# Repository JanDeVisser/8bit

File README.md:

# A Simple Ben Eater Inspired 8-bit computer

Please describe me.

### Register IDs

ID       | Register       |  R W  | Remarks
---------|----------------|-------|--------------
0000 00  | A              |  x x  |
0001 01  | B              |  x x  |
0010 02  | C              |  x x  |
0011 03  | D              |  x x  |
0100 04  | ALU LHS/Result |  x x  | Put: LHS, Get: Result
0101 05  | ALU Operation  |  - x  | Put: RHS, OP0-3: Operation
0110 06  | Instruction    |  - x  |
0111 07  | Mem            |  x x  |
1000 08  | Prog Counter   |  x x  |
1001 09  | SP             |  x x  |
1010 10  | Si             |  x x  |
1011 11  | Di             |  x x  |
1100 12  | TX             |       |
1101 13  |                |       |
1110 14	 | Monitor        |  x -  |
1111 15  | Mem Addr       |  - x  |

### Control Lines

Pin   | Name                   | Description
------|------------------------|-----------------------
1     | `GND`                  | Common Ground
2     | `VCC`                  | +5V Power
3     | `CLK`                  | Square Wave Clock
4     | ~~`CLK`~~              | Reverse Clock
5     | `^CLK`                 | "Burst" Clock at rising edge of CLK
6     | `HLT`                  | Halts clock
7     | ~~`SUS`~~              | Requests Control Unit to cease dispatching instructions.
8     | ~~`XDATA`~~            | 8 bit Data transfer instruction
9     | ~~`XADDR`~~            | 16 bit address transfer instruction
10    | ~~`SACK`~~             | Set by Control Unit as acknowlegement of SUS.
11-14 | `OP0`-`OP3`            | Custom Operation codes used by various instructions. See below.
15    | `RST`                  | Reset
16    | ~~`IO`~~               | In/Out instruction
17-20 | `PUT0`-`PUT3`          | Register ID of the target of a transfer instruction.
21-24 | `GET0`-`GET3`          | Register ID of the source of a transfer instruction.
25-32 | `D0`-`D7`              | Databus
33-40 | `A0`-`A7` / `A8`-`A15` | Address bus

### Operation Codes

#### XADDR

OP0-3 |Function
---|---
`XX01`|Increment source (Get) register
`XX10`|Decrement source (Get) register

#### XDATA

_When moving data between 8- and 16-bit registers:_

OP0-3 |Function
------|--------
`XXX0`|Transfer to/from the LSB of the 16-bit register
`XXX1`|Transfer to/from the MSB of the 16-bit register

_When the target register is ALU Operation (`0x5`):_

OP0-3|Operation
-----|-----------
`0x0`|`ADD`
`0x1`|`ADC`
`0x2`|`SUB`
`0x3`|`SBB`
...|...
`0x8`|`AND`
`0x9`|`OR`
`0xA`|`XOR`
`0xB`|`NOT LHS`
`0xC`|`SHL`
`0xD`|`SHR`
`0xE`|`CLR`
...|...

## N O T E S

### SBB (Subtract with Borrow)

See here: https://en.wikipedia.org/wiki/Carry_flag#Vs._borrow_flag

We use the convention that when subtracting the processor Carry flag is a borrow flag. This is in line with the Z80 and x68.

### 74xxx253 Function Table

As determined by Julian Ilett in https://www.youtube.com/watch?v=15M63Zqkthk

C3-C0 :arrow_down: BA :arrow_right: | 11 | 10 | 01 | 00 | Operation
------|----|----|----|----|-----------
  0x0  | 0  | 0  | 0  | 0  | All Zero
  0x1  | 0  | 0  | 0  | 1  | A NOR B
  0x2  | 0  | 0  | 1  | 0  | A AND (NOT B)
  0x3  | 0  | 0  | 1  | 1  | NOT B
  0x4  | 0  | 1  | 0  | 0  | (NOT A) AND B
  0x5  | 0  | 1  | 0  | 1  | NOT A
  0x6  | 0  | 1  | 1  | 0  | A XOR B
  0x7  | 0  | 1  | 1  | 1  | A NAND B
  0x8  | 1  | 0  | 0  | 0  | A AND B
  0x9  | 1  | 0  | 0  | 1  | A XNOR B
  0xA  | 1  | 0  | 1  | 0  | A
  0xB  | 1  | 0  | 1  | 1  | A OR (NOT B)
  0xC  | 1  | 1  | 0  | 0  | B
  0xD  | 1  | 1  | 0  | 1  | (NOT A) OR B
  0xE  | 1  | 1  | 1  | 0  | A OR B
  0xF  | 1  | 1  | 1  | 1  | All One

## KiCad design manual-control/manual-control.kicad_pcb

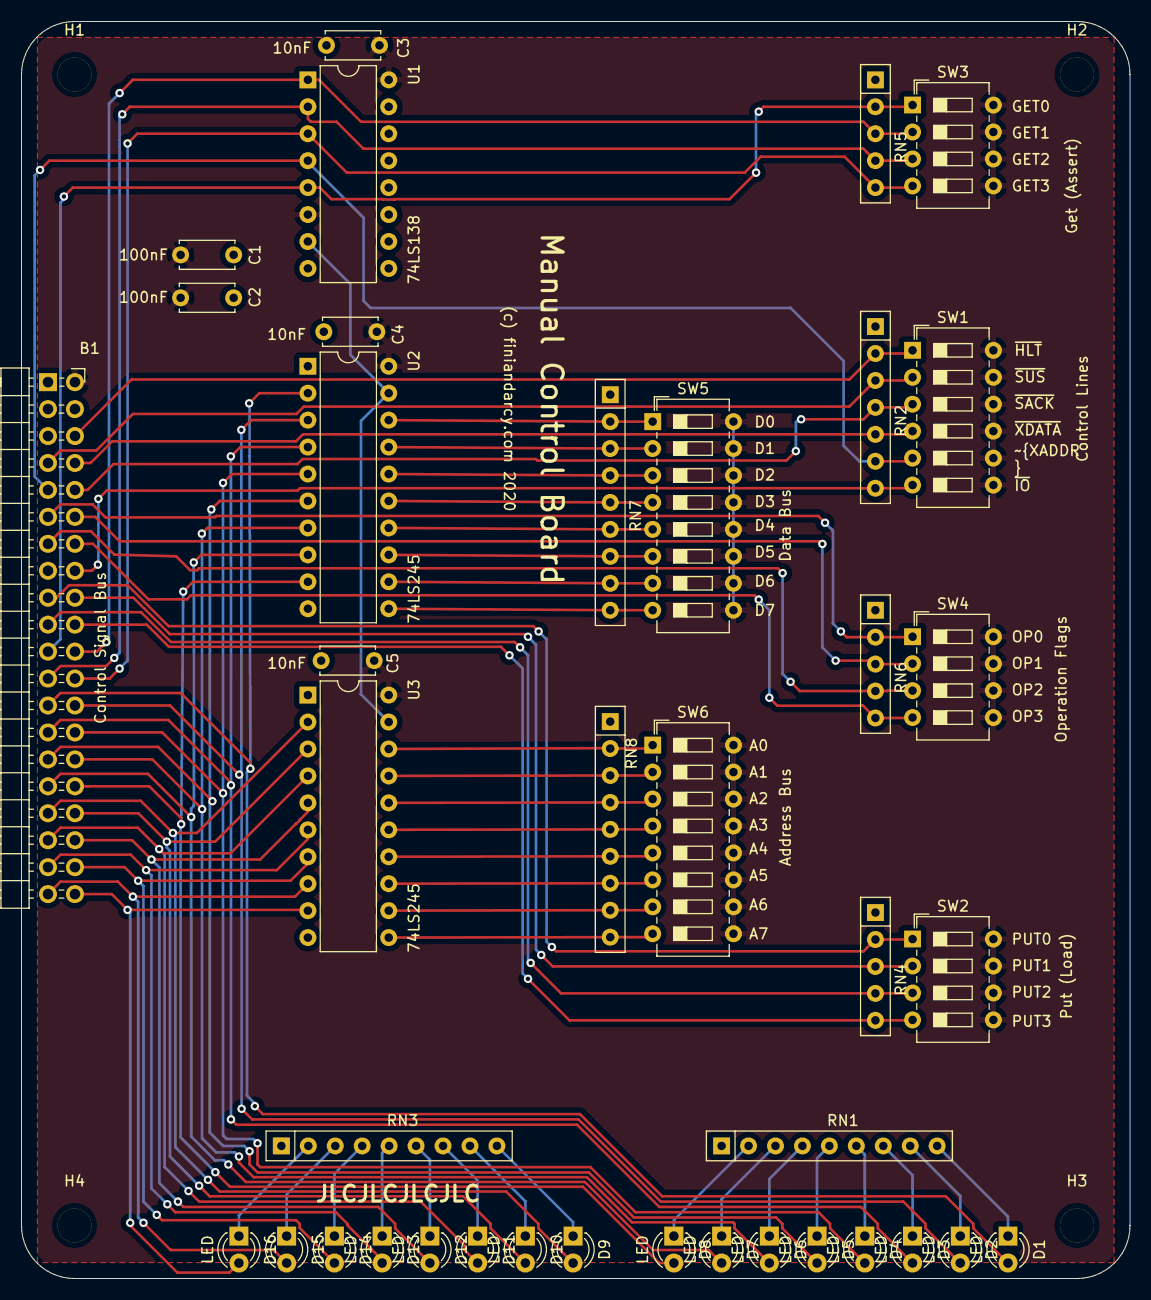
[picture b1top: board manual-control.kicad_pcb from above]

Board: 2 copper layers, 104.5 x 118.5 mm, 43 parts (0 on the bottom side), 69 nets.

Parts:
B1: Control Signal Bus; PinHeader_2x20_P2.54mm_Horizontal_Flipped
C1, C2: 100nF; C_Disc_D5.0mm_W2.5mm_P5.00mm
C3, C4, C5: 10nF; C_Disc_D5.0mm_W2.5mm_P5.00mm
D1, D2, D3, D4, D5, D6, D7, D8, D9, D10, D11, D12, D13, D14, D15, D16: LED; LED_D3.0mm
H1, H2, H3, H4: H; MountingHole_3.2mm_M3
RN1, RN3, RN7, RN8: 1K; R_Array_SIP9
RN2: 1K; R_Array_SIP7
RN4, RN5, RN6: 1K; R_Array_SIP5
SW1: Control Lines; SW_DIP_SPSTx06_Slide_6.7x16.8mm_W7.62mm_P2.54mm_LowProfile
SW2: Put (Load); SW_DIP_SPSTx04_Slide_6.7x11.72mm_W7.62mm_P2.54mm_LowProfile
SW3: Get (Assert); SW_DIP_SPSTx04_Slide_6.7x11.72mm_W7.62mm_P2.54mm_LowProfile
SW4: Operation Flags; SW_DIP_SPSTx04_Slide_6.7x11.72mm_W7.62mm_P2.54mm_LowProfile
SW5: Data Bus; SW_DIP_SPSTx08_Slide_6.7x21.88mm_W7.62mm_P2.54mm_LowProfile
SW6: Address Bus; SW_DIP_SPSTx08_Slide_6.7x21.88mm_W7.62mm_P2.54mm_LowProfile
U1: 74LS138; DIP-16_W7.62mm
U2, U3: 74LS245; DIP-20_W7.62mm

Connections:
/A0: B1.33, D9.2, U3.2
/A1: B1.34, D10.2, U3.3
/A2: B1.35, D11.2, U3.4
/A3: B1.36, D12.2, U3.5
/A4: B1.37, D13.2, U3.6
/A5: B1.38, D14.2, U3.7
/A6: B1.39, D15.2, U3.8
/A7: B1.40, D16.2, U3.9
/D0: B1.25, D1.2, U2.2
/D1: B1.26, D2.2, U2.3
/D2: B1.27, D3.2, U2.4
/D3: B1.28, D4.2, U2.5
/D4: B1.29, D5.2, U2.6
/D5: B1.30, D6.2, U2.7
/D6: B1.31, D7.2, U2.8
/D7: B1.32, D8.2, U2.9
/GET0: B1.21, RN5.2, SW3.1, U1.5
/GET1: B1.22, RN5.3, SW3.2, U1.1
/GET2: B1.23, RN5.4, SW3.3, U1.2
/GET3: B1.24, RN5.5, SW3.4, U1.3
/OP0: B1.11, RN6.2, SW4.1
/OP1: B1.12, RN6.3, SW4.2
/OP2: B1.13, RN6.4, SW4.3
/OP3: B1.14, RN6.5, SW4.4
/PUT0: B1.17, RN4.2, SW2.1
/PUT1: B1.18, RN4.3, SW2.2
/PUT2: B1.19, RN4.4, SW2.3
/PUT3: B1.20, RN4.5, SW2.4
/~Get: U1.7, U2.19, U3.19
/~HLT: B1.6, RN2.2, SW1.1
/~IO: B1.16, RN2.7, SW1.6
/~SACK: B1.10, RN2.4, SW1.3
/~SUS: B1.7, RN2.3, SW1.2
/~XADDR: B1.9, RN2.6, SW1.5, U1.4
/~XDATA: B1.8, RN2.5, SW1.4
GND: B1.1, C1.2, C2.2, C3.1, C4.1, C5.1, H1.1, H2.1, H3.1, H4.1, RN1.1, RN2.1, RN3.1, RN4.1, RN5.1, RN6.1, RN7.1, RN8.1, U1.8, U2.1, U2.10, U3.1, U3.10
unnamed: D1.1, RN1.9
unnamed: D2.1, RN1.8
unnamed: D3.1, RN1.7
unnamed: D4.1, RN1.6
unnamed: D5.1, RN1.5
unnamed: D6.1, RN1.4
unnamed: D7.1, RN1.3
unnamed: D8.1, RN1.2
unnamed: D9.1, RN3.9
unnamed: D10.1, RN3.8
unnamed: D11.1, RN3.7
unnamed: D12.1, RN3.6
unnamed: D13.1, RN3.5
unnamed: D14.1, RN3.4
unnamed: D15.1, RN3.3
unnamed: D16.1, RN3.2
unnamed: RN7.2, SW5.1, U2.18
unnamed: RN7.3, SW5.2, U2.17
unnamed: RN7.4, SW5.3, U2.16
unnamed: RN7.5, SW5.4, U2.15
unnamed: RN7.6, SW5.5, U2.14
unnamed: RN7.7, SW5.6, U2.13
unnamed: RN7.8, SW5.7, U2.12
unnamed: RN7.9, SW5.8, U2.11
unnamed: RN8.2, SW6.1, U3.18
unnamed: RN8.3, SW6.2, U3.17
unnamed: RN8.4, SW6.3, U3.16
unnamed: RN8.5, SW6.4, U3.15
unnamed: RN8.6, SW6.5, U3.14
unnamed: RN8.7, SW6.6, U3.13
unnamed: RN8.8, SW6.7, U3.12
unnamed: RN8.9, SW6.8, U3.11
VCC: B1.2, C1.1, C2.1, C3.2, C4.2, C5.2, SW1.7, SW1.8, SW1.9, SW1.10, SW1.11, SW1.12, SW2.5, SW2.6, SW2.7, SW2.8, SW3.5, SW3.6, SW3.7, SW3.8, SW4.5, SW4.6, SW4.7, SW4.8, SW5.9, SW5.10, SW5.11, SW5.12, SW5.13, SW5.14, SW5.15, SW5.16, SW6.9, SW6.10, SW6.11, SW6.12, SW6.13, SW6.14, SW6.15, SW6.16, U1.6, U1.16, U2.20, U3.20

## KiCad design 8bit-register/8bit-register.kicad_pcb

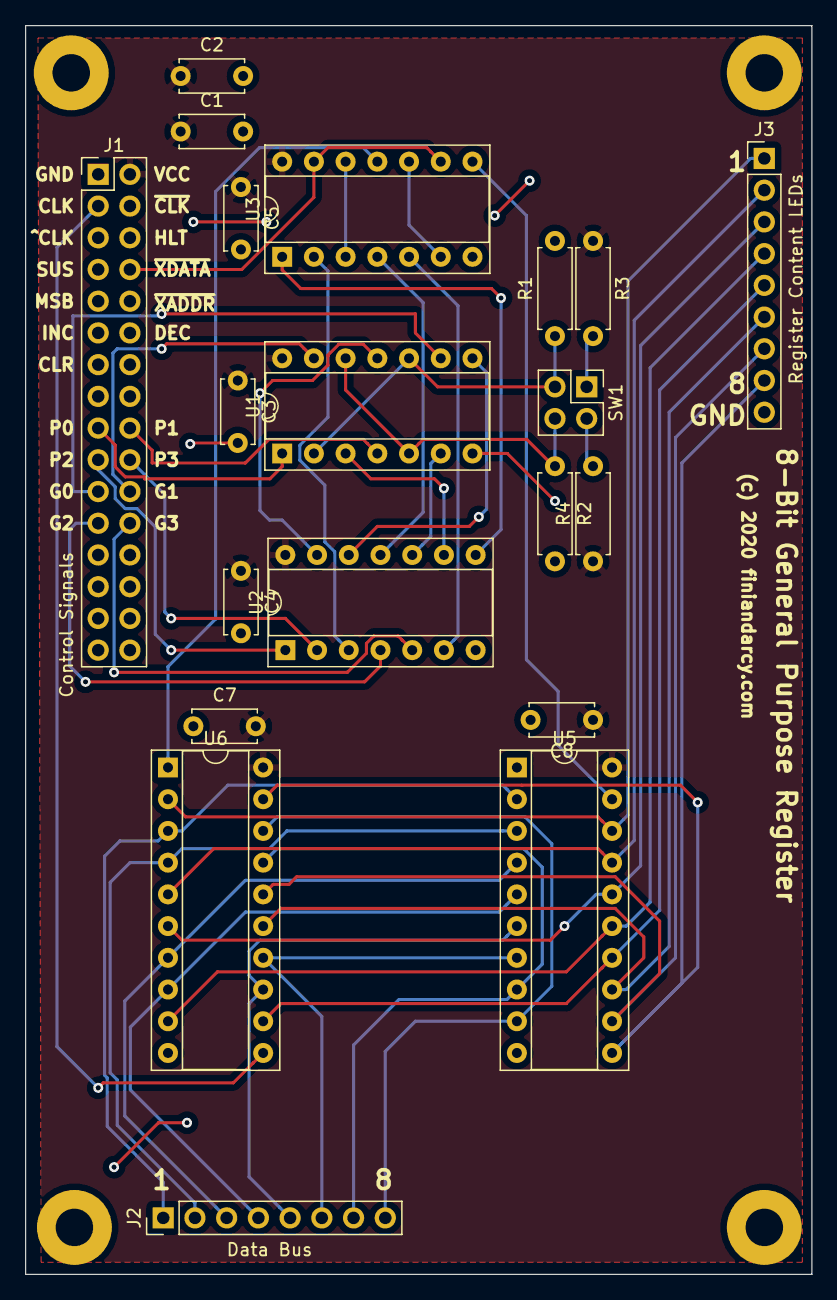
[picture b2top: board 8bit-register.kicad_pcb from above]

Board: 2 copper layers, 63.0 x 100.0 mm, 24 parts (0 on the bottom side), 44 nets.

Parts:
C1, C2: 0.1uF; C_Disc_D5.0mm_W2.5mm_P5.00mm
C3, C4, C5, C7, C8: 10nF; C_Disc_D5.0mm_W2.5mm_P5.00mm
J1: Control Signals; PinHeader_2x16_P2.54mm_Vertical
J2: Data Bus; PinHeader_1x08_P2.54mm_Vertical
J3: Register Content LEDs; PinHeader_1x09_P2.54mm_Vertical
M1, M2, M3, M4: MountingHole_3mm_Pad
R1, R2, R3: 3K3; R_Axial_DIN0207_L6.3mm_D2.5mm_P7.62mm_Horizontal
R4: 3k3; R_Axial_DIN0207_L6.3mm_D2.5mm_P7.62mm_Horizontal
SW1: RegisterID; PinHeader_2x02_P2.54mm_Vertical
U1: 74LS86; DIP-14_W7.62mm_Socket
U2, U3: 74LS32; DIP-14_W7.62mm_Socket
U5: 74LS245; DIP-20_W7.62mm_Socket
U6: 74LS377; DIP-20_W7.62mm_Socket

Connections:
/B0: J2.1, U5.2, U6.3
/B1: J2.2, U5.3, U6.4
/B2: J2.3, U5.4, U6.7
/B3: J2.4, U5.5, U6.8
/B4: J2.5, U5.6, U6.13
/B5: J2.6, U5.7, U6.14
/B6: J2.7, U5.8, U6.17
/B7: J2.8, U5.9, U6.18
/CLK: J1.3, U6.11
/Conf0: R1.1, SW1.3, U1.2, U1.10
/Conf1: R2.1, SW1.4, U1.5, U1.12
/GET0: J1.21, U1.9
/GET1: J1.22, U1.13
/GET2: J1.23, U2.4
/GET3: J1.24, U2.5
/PUT0: J1.17, U1.1
/PUT1: J1.18, U1.4
/PUT2: J1.19, U2.1
/PUT3: J1.20, U2.2
/T0: J3.1, U5.18, U6.2
/T1: J3.2, U5.17, U6.5
/T2: J3.3, U5.16, U6.6
/T3: J3.4, U5.15, U6.9
/T4: J3.5, U5.14, U6.12
/T5: J3.6, U5.13, U6.15
/T6: J3.7, U5.12, U6.16
/T7: J3.8, U5.11, U6.19
/~Get: U3.8, U5.19
/~Put: U3.11, U6.1
/~XDATA: J1.8, U3.9, U3.13
GND: C1.2, C2.2, C3.2, C4.2, C5.2, C7.1, C8.2, J1.1, J3.9, R1.2, R2.2, U1.7, U2.7, U3.7, U5.1, U5.10, U6.10
unnamed: R3.2, SW1.1
unnamed: R4.2, SW1.2
unnamed: U1.3, U2.9
unnamed: U1.6, U2.10
unnamed: U1.8, U2.12
unnamed: U1.11, U2.13
unnamed: U2.3, U3.2
unnamed: U2.6, U3.5
unnamed: U2.8, U3.1
unnamed: U2.11, U3.4
unnamed: U3.6, U3.10
unnamed: U3.3, U3.12
VCC: C1.1, C2.1, C3.1, C4.1, C5.1, C7.2, C8.1, J1.2, R3.1, R4.1, U1.14, U2.14, U3.14, U5.20, U6.20

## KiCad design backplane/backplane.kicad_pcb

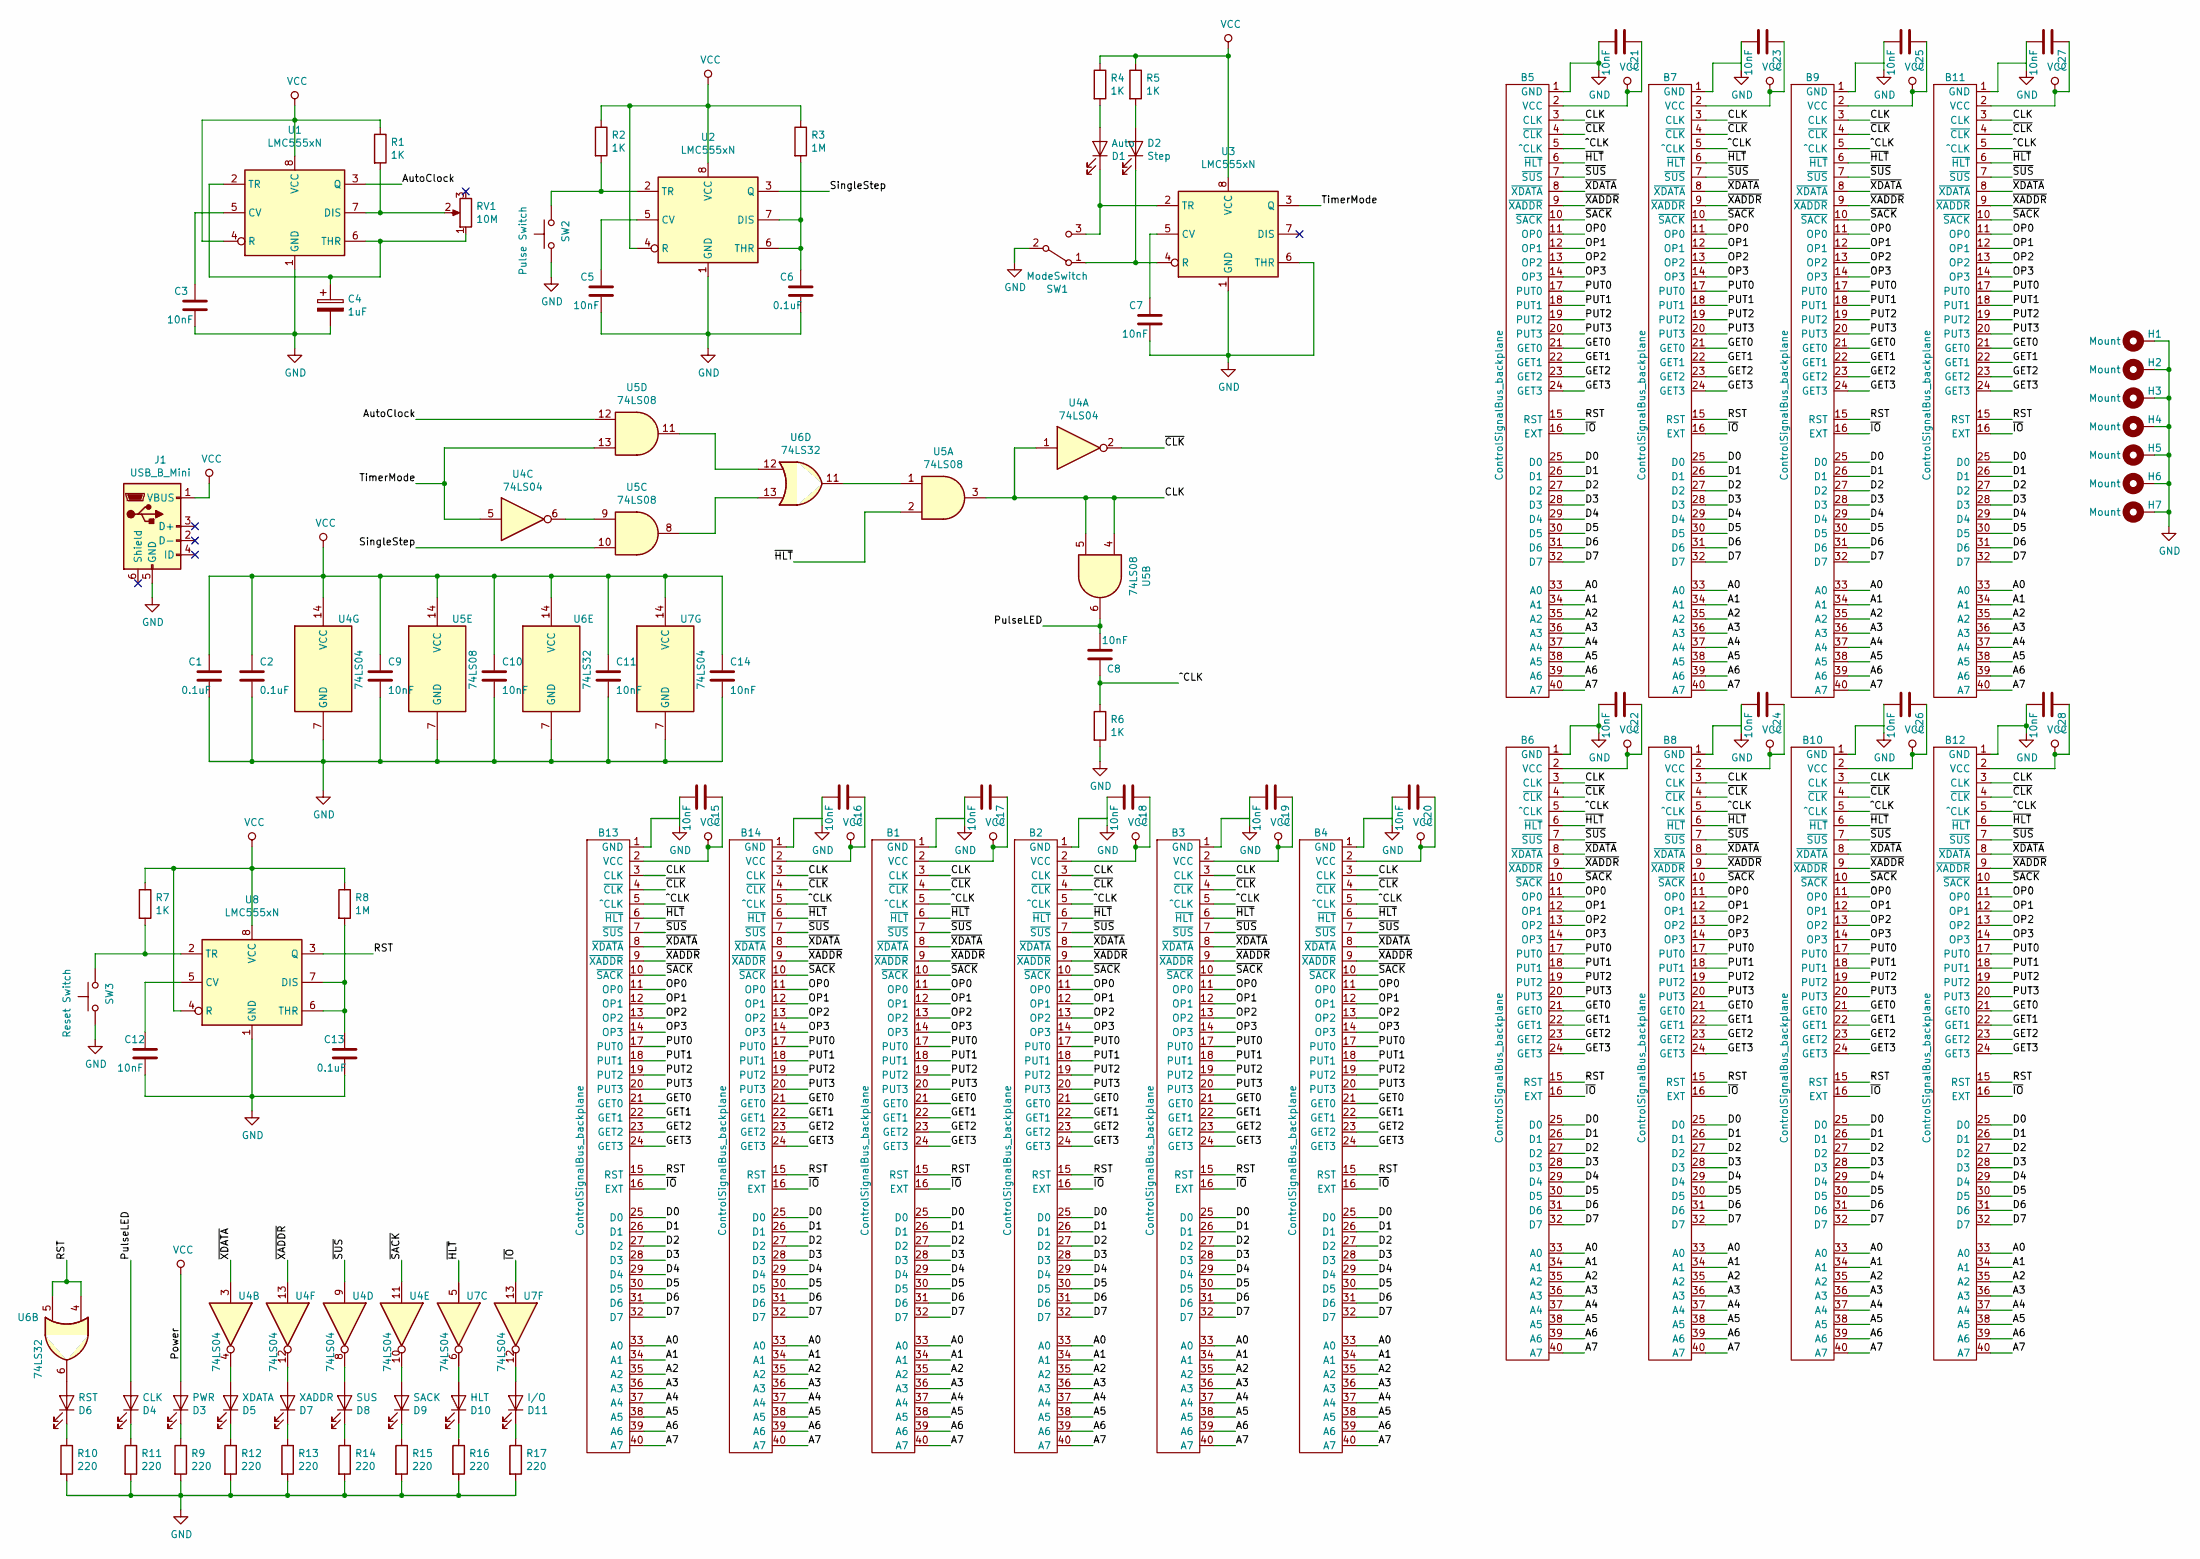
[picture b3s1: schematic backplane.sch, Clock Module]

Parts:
B1, B2, B3, B4, B5, B6, B7, B8, B9, B10, B11, B12, B13, B14: ControlSignalBus_backplane; PinSocket_2x20_P2.54mm_Vertical
C1, C2, C6, C13: 0.1uF; C_Disc_D5.0mm_W2.5mm_P5.00mm
C3, C5, C7, C8, C9, C10, C11, C12, C14, C15, C16, C17, C18, C19, C20, C21, C22, C23, C24, C25, C26, C27, C28: 10nF; C_Disc_D5.0mm_W2.5mm_P5.00mm
C4: 1uF; C_Radial_D5.0mm_H11.0mm_P2.00mm
D1: Auto; LED_D5.0mm
D2: Step; LED_D5.0mm
D3: PWR; LED_D5.0mm
D4: CLK; LED_D5.0mm
D5: XDATA; LED_D5.0mm
D6: RST; LED_D5.0mm
D7: XADDR; LED_D5.0mm
D8: SUS; LED_D5.0mm
D9: SACK; LED_D5.0mm
D10: HLT; LED_D5.0mm
D11: I/O; LED_D5.0mm
H1, H2, H3, H4, H5, H6, H7: Mount; MountingHole_3.2mm_M3_Pad
J1: USB_B_Mini; TE_2172034-1
R1, R2, R4, R5, R6, R7: 1K; R_Axial_DIN0207_L6.3mm_D2.5mm_P7.62mm_Horizontal
R3, R8: 1M; R_Axial_DIN0207_L6.3mm_D2.5mm_P7.62mm_Horizontal
R9, R10, R11, R12, R13, R14, R15, R16, R17: 220; R_Axial_DIN0207_L6.3mm_D2.5mm_P7.62mm_Horizontal
RV1: 10M; TT-P160KN-0QC15A
SW1: ModeSwitch; 400MSP1R6BLKM6RE
SW2: Pulse Switch; KS11R22CQD
SW3: Reset Switch; KS11R22CQD
U1, U2, U3, U8: LMC555xN; DIP-8_W7.62mm_Socket
U4, U7: 74LS04; DIP-14_W7.62mm_Socket
U5: 74LS08; DIP-14_W7.62mm_Socket
U6: 74LS32; DIP-14_W7.62mm_Socket

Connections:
/A0: B1.33 (A0), B2.33 (A0), B3.33 (A0), B4.33 (A0), B5.33 (A0), B6.33 (A0), B7.33 (A0), B8.33 (A0), B9.33 (A0), B10.33 (A0), B11.33 (A0), B12.33 (A0), B13.33 (A0), B14.33 (A0)
/A1: B1.34 (A1), B2.34 (A1), B3.34 (A1), B4.34 (A1), B5.34 (A1), B6.34 (A1), B7.34 (A1), B8.34 (A1), B9.34 (A1), B10.34 (A1), B11.34 (A1), B12.34 (A1), B13.34 (A1), B14.34 (A1)
/A2: B1.35 (A2), B2.35 (A2), B3.35 (A2), B4.35 (A2), B5.35 (A2), B6.35 (A2), B7.35 (A2), B8.35 (A2), B9.35 (A2), B10.35 (A2), B11.35 (A2), B12.35 (A2), B13.35 (A2), B14.35 (A2)
/A3: B1.36 (A3), B2.36 (A3), B3.36 (A3), B4.36 (A3), B5.36 (A3), B6.36 (A3), B7.36 (A3), B8.36 (A3), B9.36 (A3), B10.36 (A3), B11.36 (A3), B12.36 (A3), B13.36 (A3), B14.36 (A3)
/A4: B1.37 (A4), B2.37 (A4), B3.37 (A4), B4.37 (A4), B5.37 (A4), B6.37 (A4), B7.37 (A4), B8.37 (A4), B9.37 (A4), B10.37 (A4), B11.37 (A4), B12.37 (A4), B13.37 (A4), B14.37 (A4)
/A5: B1.38 (A5), B2.38 (A5), B3.38 (A5), B4.38 (A5), B5.38 (A5), B6.38 (A5), B7.38 (A5), B8.38 (A5), B9.38 (A5), B10.38 (A5), B11.38 (A5), B12.38 (A5), B13.38 (A5), B14.38 (A5)
/A6: B1.39 (A6), B2.39 (A6), B3.39 (A6), B4.39 (A6), B5.39 (A6), B6.39 (A6), B7.39 (A6), B8.39 (A6), B9.39 (A6), B10.39 (A6), B11.39 (A6), B12.39 (A6), B13.39 (A6), B14.39 (A6)
/A7: B1.40 (A7), B2.40 (A7), B3.40 (A7), B4.40 (A7), B5.40 (A7), B6.40 (A7), B7.40 (A7), B8.40 (A7), B9.40 (A7), B10.40 (A7), B11.40 (A7), B12.40 (A7), B13.40 (A7), B14.40 (A7)
/AutoClock: U1.3 (Q), U5.12
/CLK: B1.3 (CLK), B2.3 (CLK), B3.3 (CLK), B4.3 (CLK), B5.3 (CLK), B6.3 (CLK), B7.3 (CLK), B8.3 (CLK), B9.3 (CLK), B10.3 (CLK), B11.3 (CLK), B12.3 (CLK), B13.3 (CLK), B14.3 (CLK), U4.1, U5.3, U5.4, U5.5
/D0: B1.25 (D0), B2.25 (D0), B3.25 (D0), B4.25 (D0), B5.25 (D0), B6.25 (D0), B7.25 (D0), B8.25 (D0), B9.25 (D0), B10.25 (D0), B11.25 (D0), B12.25 (D0), B13.25 (D0), B14.25 (D0)
/D1: B1.26 (D1), B2.26 (D1), B3.26 (D1), B4.26 (D1), B5.26 (D1), B6.26 (D1), B7.26 (D1), B8.26 (D1), B9.26 (D1), B10.26 (D1), B11.26 (D1), B12.26 (D1), B13.26 (D1), B14.26 (D1)
/D2: B1.27 (D2), B2.27 (D2), B3.27 (D2), B4.27 (D2), B5.27 (D2), B6.27 (D2), B7.27 (D2), B8.27 (D2), B9.27 (D2), B10.27 (D2), B11.27 (D2), B12.27 (D2), B13.27 (D2), B14.27 (D2)
/D3: B1.28 (D3), B2.28 (D3), B3.28 (D3), B4.28 (D3), B5.28 (D3), B6.28 (D3), B7.28 (D3), B8.28 (D3), B9.28 (D3), B10.28 (D3), B11.28 (D3), B12.28 (D3), B13.28 (D3), B14.28 (D3)
/D4: B1.29 (D4), B2.29 (D4), B3.29 (D4), B4.29 (D4), B5.29 (D4), B6.29 (D4), B7.29 (D4), B8.29 (D4), B9.29 (D4), B10.29 (D4), B11.29 (D4), B12.29 (D4), B13.29 (D4), B14.29 (D4)
/D5: B1.30 (D5), B2.30 (D5), B3.30 (D5), B4.30 (D5), B5.30 (D5), B6.30 (D5), B7.30 (D5), B8.30 (D5), B9.30 (D5), B10.30 (D5), B11.30 (D5), B12.30 (D5), B13.30 (D5), B14.30 (D5)
/D6: B1.31 (D6), B2.31 (D6), B3.31 (D6), B4.31 (D6), B5.31 (D6), B6.31 (D6), B7.31 (D6), B8.31 (D6), B9.31 (D6), B10.31 (D6), B11.31 (D6), B12.31 (D6), B13.31 (D6), B14.31 (D6)
/D7: B1.32 (D7), B2.32 (D7), B3.32 (D7), B4.32 (D7), B5.32 (D7), B6.32 (D7), B7.32 (D7), B8.32 (D7), B9.32 (D7), B10.32 (D7), B11.32 (D7), B12.32 (D7), B13.32 (D7), B14.32 (D7)
/GET0: B1.21 (GET0), B2.21 (GET0), B3.21 (GET0), B4.21 (GET0), B5.21 (GET0), B6.21 (GET0), B7.21 (GET0), B8.21 (GET0), B9.21 (GET0), B10.21 (GET0), B11.21 (GET0), B12.21 (GET0), B13.21 (GET0), B14.21 (GET0)
/GET1: B1.22 (GET1), B2.22 (GET1), B3.22 (GET1), B4.22 (GET1), B5.22 (GET1), B6.22 (GET1), B7.22 (GET1), B8.22 (GET1), B9.22 (GET1), B10.22 (GET1), B11.22 (GET1), B12.22 (GET1), B13.22 (GET1), B14.22 (GET1)
/GET2: B1.23 (GET2), B2.23 (GET2), B3.23 (GET2), B4.23 (GET2), B5.23 (GET2), B6.23 (GET2), B7.23 (GET2), B8.23 (GET2), B9.23 (GET2), B10.23 (GET2), B11.23 (GET2), B12.23 (GET2), B13.23 (GET2), B14.23 (GET2)
/GET3: B1.24 (GET3), B2.24 (GET3), B3.24 (GET3), B4.24 (GET3), B5.24 (GET3), B6.24 (GET3), B7.24 (GET3), B8.24 (GET3), B9.24 (GET3), B10.24 (GET3), B11.24 (GET3), B12.24 (GET3), B13.24 (GET3), B14.24 (GET3)
/OP0: B1.11 (OP0), B2.11 (OP0), B3.11 (OP0), B4.11 (OP0), B5.11 (OP0), B6.11 (OP0), B7.11 (OP0), B8.11 (OP0), B9.11 (OP0), B10.11 (OP0), B11.11 (OP0), B12.11 (OP0), B13.11 (OP0), B14.11 (OP0)
/OP1: B1.12 (OP1), B2.12 (OP1), B3.12 (OP1), B4.12 (OP1), B5.12 (OP1), B6.12 (OP1), B7.12 (OP1), B8.12 (OP1), B9.12 (OP1), B10.12 (OP1), B11.12 (OP1), B12.12 (OP1), B13.12 (OP1), B14.12 (OP1)
/OP2: B1.13 (OP2), B2.13 (OP2), B3.13 (OP2), B4.13 (OP2), B5.13 (OP2), B6.13 (OP2), B7.13 (OP2), B8.13 (OP2), B9.13 (OP2), B10.13 (OP2), B11.13 (OP2), B12.13 (OP2), B13.13 (OP2), B14.13 (OP2)
/OP3: B1.14 (OP3), B2.14 (OP3), B3.14 (OP3), B4.14 (OP3), B5.14 (OP3), B6.14 (OP3), B7.14 (OP3), B8.14 (OP3), B9.14 (OP3), B10.14 (OP3), B11.14 (OP3), B12.14 (OP3), B13.14 (OP3), B14.14 (OP3)
/PUT0: B1.17 (PUT0), B2.17 (PUT0), B3.17 (PUT0), B4.17 (PUT0), B5.17 (PUT0), B6.17 (PUT0), B7.17 (PUT0), B8.17 (PUT0), B9.17 (PUT0), B10.17 (PUT0), B11.17 (PUT0), B12.17 (PUT0), B13.17 (PUT0), B14.17 (PUT0)
/PUT1: B1.18 (PUT1), B2.18 (PUT1), B3.18 (PUT1), B4.18 (PUT1), B5.18 (PUT1), B6.18 (PUT1), B7.18 (PUT1), B8.18 (PUT1), B9.18 (PUT1), B10.18 (PUT1), B11.18 (PUT1), B12.18 (PUT1), B13.18 (PUT1), B14.18 (PUT1)
/PUT2: B1.19 (PUT2), B2.19 (PUT2), B3.19 (PUT2), B4.19 (PUT2), B5.19 (PUT2), B6.19 (PUT2), B7.19 (PUT2), B8.19 (PUT2), B9.19 (PUT2), B10.19 (PUT2), B11.19 (PUT2), B12.19 (PUT2), B13.19 (PUT2), B14.19 (PUT2)
/PUT3: B1.20 (PUT3), B2.20 (PUT3), B3.20 (PUT3), B4.20 (PUT3), B5.20 (PUT3), B6.20 (PUT3), B7.20 (PUT3), B8.20 (PUT3), B9.20 (PUT3), B10.20 (PUT3), B11.20 (PUT3), B12.20 (PUT3), B13.20 (PUT3), B14.20 (PUT3)
/PulseLED: C8.2, D4.2 (A), U5.6
/RST: B1.15 (RST), B2.15 (RST), B3.15 (RST), B4.15 (RST), B5.15 (RST), B6.15 (RST), B7.15 (RST), B8.15 (RST), B9.15 (RST), B10.15 (RST), B11.15 (RST), B12.15 (RST), B13.15 (RST), B14.15 (RST), U6.4, U6.5, U8.3 (Q)
/SingleStep: U2.3 (Q), U5.10
/TimerMode: U3.3 (Q), U4.5, U5.13
/^CLK: B1.5 (^CLK), B2.5 (^CLK), B3.5 (^CLK), B4.5 (^CLK), B5.5 (^CLK), B6.5 (^CLK), B7.5 (^CLK), B8.5 (^CLK), B9.5 (^CLK), B10.5 (^CLK), B11.5 (^CLK), B12.5 (^CLK), B13.5 (^CLK), B14.5 (^CLK), C8.1, R6.1
/~CLK: B1.4 (~CLK), B2.4 (~CLK), B3.4 (~CLK), B4.4 (~CLK), B5.4 (~CLK), B6.4 (~CLK), B7.4 (~CLK), B8.4 (~CLK), B9.4 (~CLK), B10.4 (~CLK), B11.4 (~CLK), B12.4 (~CLK), B13.4 (~CLK), B14.4 (~CLK), U4.2
/~HLT: B1.6 (~HLT), B2.6 (~HLT), B3.6 (~HLT), B4.6 (~HLT), B5.6 (~HLT), B6.6 (~HLT), B7.6 (~HLT), B8.6 (~HLT), B9.6 (~HLT), B10.6 (~HLT), B11.6 (~HLT), B12.6 (~HLT), B13.6 (~HLT), B14.6 (~HLT), U5.2, U7.5
/~IO: B1.16 (EXT), B2.16 (EXT), B3.16 (EXT), B4.16 (EXT), B5.16 (EXT), B6.16 (EXT), B7.16 (EXT), B8.16 (EXT), B9.16 (EXT), B10.16 (EXT), B11.16 (EXT), B12.16 (EXT), B13.16 (EXT), B14.16 (EXT), U7.13
/~SACK: B1.10 (~SACK), B2.10 (~SACK), B3.10 (~SACK), B4.10 (~SACK), B5.10 (~SACK), B6.10 (~SACK), B7.10 (~SACK), B8.10 (~SACK), B9.10 (~SACK), B10.10 (~SACK), B11.10 (~SACK), B12.10 (~SACK), B13.10 (~SACK), B14.10 (~SACK), U4.11
/~SUS: B1.7 (~SUS), B2.7 (~SUS), B3.7 (~SUS), B4.7 (~SUS), B5.7 (~SUS), B6.7 (~SUS), B7.7 (~SUS), B8.7 (~SUS), B9.7 (~SUS), B10.7 (~SUS), B11.7 (~SUS), B12.7 (~SUS), B13.7 (~SUS), B14.7 (~SUS), U4.9
/~XADDR: B1.9 (~XADDR), B2.9 (~XADDR), B3.9 (~XADDR), B4.9 (~XADDR), B5.9 (~XADDR), B6.9 (~XADDR), B7.9 (~XADDR), B8.9 (~XADDR), B9.9 (~XADDR), B10.9 (~XADDR), B11.9 (~XADDR), B12.9 (~XADDR), B13.9 (~XADDR), B14.9 (~XADDR), U4.13
/~XDATA: B1.8 (~XDATA), B2.8 (~XDATA), B3.8 (~XDATA), B4.8 (~XDATA), B5.8 (~XDATA), B6.8 (~XDATA), B7.8 (~XDATA), B8.8 (~XDATA), B9.8 (~XDATA), B10.8 (~XDATA), B11.8 (~XDATA), B12.8 (~XDATA), B13.8 (~XDATA), B14.8 (~XDATA), U4.3
GND: B1.1 (GND), B2.1 (GND), B3.1 (GND), B4.1 (GND), B5.1 (GND), B6.1 (GND), B7.1 (GND), B8.1 (GND), B9.1 (GND), B10.1 (GND), B11.1 (GND), B12.1 (GND), B13.1 (GND), B14.1 (GND), C1.2, C2.2, C3.2, C4.2, C5.2, C6.2, C7.2, C9.2, C10.2, C11.2, C12.2, C13.2, C14.2, C15.2, C16.2, C17.2, C18.2, C19.2, C20.2, C21.2, C22.2, C23.2, C24.2, C25.2, C26.2, C27.2, C28.2, H1.1, H2.1, H3.1, H4.1, H5.1, H6.1, H7.1, J1.5 (GND), R6.2, R9.2, R10.2, R11.2, R12.2, R13.2, R14.2, R15.2, R16.2, R17.2, SW1.2 (B), SW2.1, SW3.1, U1.1 (GND), U2.1 (GND), U3.1 (GND), U3.6 (THR), U4.7 (GND), U5.7 (GND), U6.7 (GND), U7.7 (GND), U8.1 (GND)
unnamed: C3.1, U1.5 (CV)
unnamed: C4.1, RV1.1, U1.2 (TR), U1.6 (THR)
unnamed: C5.1, U2.5 (CV)
unnamed: C6.1, R3.2, U2.6 (THR), U2.7 (DIS)
unnamed: C7.1, U3.5 (CV)
unnamed: C12.1, U8.5 (CV)
unnamed: C13.1, R8.2, U8.6 (THR), U8.7 (DIS)
unnamed: D1.1 (K), SW1.3 (C), U3.2 (TR)
unnamed: D1.2 (A), R4.2
unnamed: D2.1 (K), SW1.1 (A), U3.4 (R)
unnamed: D2.2 (A), R5.2
unnamed: D3.1 (K), R9.1
unnamed: D4.1 (K), R11.1
unnamed: D5.1 (K), R12.1
unnamed: D5.2 (A), U4.4
unnamed: D6.1 (K), R10.1
unnamed: D6.2 (A), U6.6
unnamed: D7.1 (K), R13.1
unnamed: D7.2 (A), U4.12
unnamed: D8.1 (K), R14.1
unnamed: D8.2 (A), U4.8
unnamed: D9.1 (K), R15.1
unnamed: D9.2 (A), U4.10
unnamed: D10.1 (K), R16.1
unnamed: D10.2 (A), U7.6
unnamed: D11.1 (K), R17.1
unnamed: D11.2 (A), U7.12
unnamed: R1.2, RV1.2, U1.7 (DIS)
unnamed: R2.2, SW2.2, U2.2 (TR)
unnamed: R7.2, SW3.2, U8.2 (TR)
unnamed: U4.6, U5.9
unnamed: U5.1, U6.11
unnamed: U5.8, U6.13
unnamed: U5.11, U6.12
VCC: B1.2 (VCC), B2.2 (VCC), B3.2 (VCC), B4.2 (VCC), B5.2 (VCC), B6.2 (VCC), B7.2 (VCC), B8.2 (VCC), B9.2 (VCC), B10.2 (VCC), B11.2 (VCC), B12.2 (VCC), B13.2 (VCC), B14.2 (VCC), C1.1, C2.1, C9.1, C10.1, C11.1, C14.1, C15.1, C16.1, C17.1, C18.1, C19.1, C20.1, C21.1, C22.1, C23.1, C24.1, C25.1, C26.1, C27.1, C28.1, D3.2 (A), J1.1 (VBUS), R1.1, R2.1, R3.1, R4.1, R5.1, R7.1, R8.1, U1.4 (R), U1.8 (VCC), U2.4 (R), U2.8 (VCC), U3.8 (VCC), U4.14 (VCC), U5.14 (VCC), U6.14 (VCC), U7.14 (VCC), U8.4 (R), U8.8 (VCC)

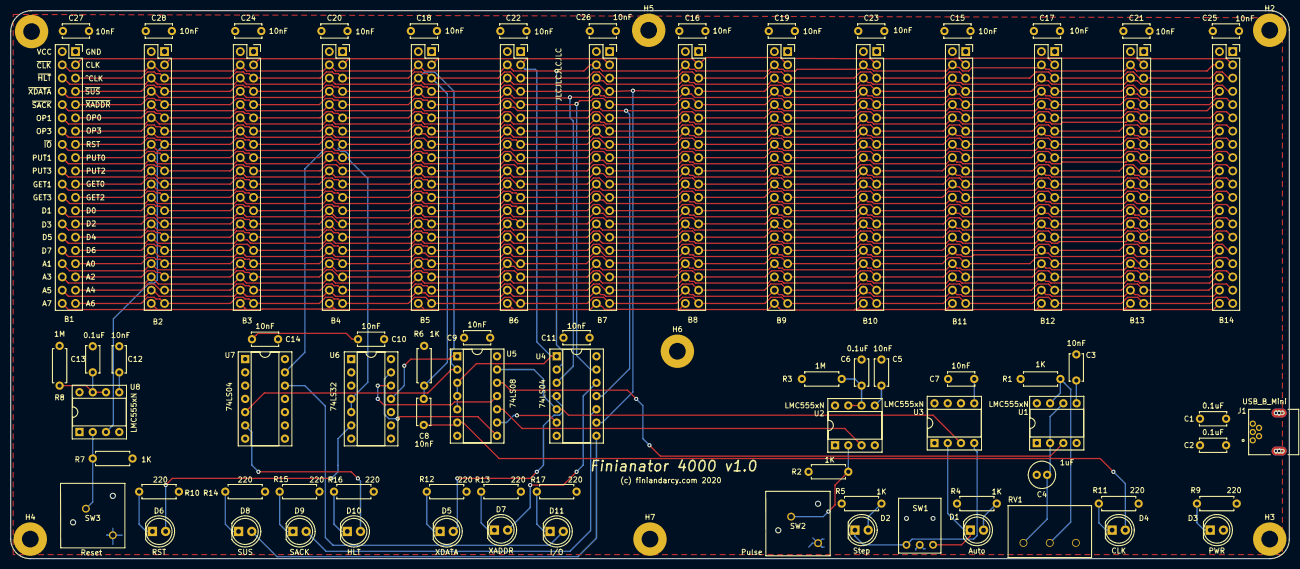
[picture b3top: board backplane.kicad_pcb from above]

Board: 2 copper layers, 245.0 x 105.0 mm, 90 parts (0 on the bottom side), 78 nets.

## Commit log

2020-06-28 Initial
2020-07-13 Documented 74xxx253 function table
2020-07-13 More writing
2020-09-16 version 1
2021-01-28 Emulator of the 8bit system.
2021-01-28 Unit tests
2021-02-01 Qt GUI
2021-02-07 Reworked Controller. It almost makes sense now
2021-02-07 Forgot some files. Added more tests
2021-02-07 Tested all GP mov x,y instructions. Fixed constant in instruction label
2021-02-07 More instructions tested
2021-02-08 JMP tested
2021-02-08 Conditional jumps tested
2021-02-08 git cleanup
2021-02-08 mov (xxxx), gp and mov (di), gp tested
2021-02-08 mov (xxxx), si|di|cd and mov (si|di), cd tested
2021-02-09 ALU - implementation, unit tests, first instruction (add a,b)
2021-02-12 ALU - more instructions, tests, bugfixes
2021-02-14 More instructions, tests, bugfixes
2021-02-16 F i B O N A C C I ! ! !
2021-02-22 Assembler first cut
2021-02-22 GUI much improved
2021-02-22 more junk excluded
2021-02-22 moved to emu
2021-02-25 Many GUI bugfixes and improvements
2021-03-01 IOChannels. Involves a bit of refactoring of the Component infrastructure.
2021-03-01 Interrupts: set NMI vector, RTI, trigger interrupt service.
2021-03-01 Interrupt was only set when debug was true
2021-03-03 More I/O, Memory refactoring
2021-03-06 GUI updates and memory banks
2021-03-08 Moved emulator separate repo

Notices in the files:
8bit-register/8bit-register.kicad_pcb:
(c) 2020 finiandarcy.com
